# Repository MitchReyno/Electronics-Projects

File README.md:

# Electronics-Projects

A collection of various electronics projects I've worked on over the years.

## Categories

- [Eurorack](#eurorack) — Modular synthesizer modules
- [Nixie](#nixie) — Nixie tube and Dekatron display projects
- [Spice Models](#spice-models) — SPICE simulation models

---

## Eurorack

Eurorack-format modular synthesizer modules, designed in KiCad.

| Project                                              | Description                                                                                                                                      |
| ---------------------------------------------------- | ------------------------------------------------------------------------------------------------------------------------------------------------ |
| [Clocky](Eurorack/Clocky/)                           | Clock divider/multiplier — 8 gate outputs (÷/× per channel), RGB LED feedback, Arduino Nano firmware. Adapted from the SoundForce Clocky design. |
| [Dual Log/Linear VCA](Eurorack/Dual_Log_Linear_VCA/) | Dual voltage-controlled amplifier with switchable logarithmic and linear response curves.                                                        |
| [Eurorack PSU](Eurorack/Eurorack_PSU/)               | Eurorack power supply unit providing ±12 V and +5 V rails for a modular case.                                                                    |
| [LFO RW](Eurorack/LFO_RW/)                           | Low-frequency oscillator module with multiple waveform outputs.                                                                                  |
| [LFO VC](Eurorack/LFO_VC/)                           | Voltage-controlled LFO with CV over rate.                                                                                                        |
| [Quad Attenuator](Eurorack/Quad_Attenuator/)         | Four-channel passive/active attenuator panel.                                                                                                    |
| [VCA](Eurorack/VCA/)                                 | Voltage-controlled amplifier module.                                                                                                             |
| [VCF State Variable](Eurorack/VCF_State_Variable/)   | State-variable voltage-controlled filter with simultaneous low-pass, band-pass, and high-pass outputs.                                           |

---

## Nixie

High-voltage power supplies and display projects for Nixie and Dekatron tubes.

| Project                                     | Description                                                        |
| ------------------------------------------- | ------------------------------------------------------------------ |
| [Dekatron PSU MK1](Nixie/Dekatron_PSU_MK1/) | High-voltage power supply designed for Dekatron counting tubes.    |
| [Nixie PSU MK1](Nixie/Nixie_PSU_MK1/)       | High-voltage boost converter power supply for Nixie tube displays. |

---

## Spice Models

[`Spice_Models/`](Spice_Models/) — A library of SPICE simulation model files (`.MOD` / `.LIB`) for common components used across projects, including transistors, diodes, op-amps, regulators, and transformers.

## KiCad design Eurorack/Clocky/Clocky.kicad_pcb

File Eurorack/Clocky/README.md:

# Clocky

A Eurorack clock divider/multiplier module, adapted from the
[SoundForce Clocky](https://soundforce.nl) design.

## Overview

This is an adapted version of the **SoundForce Clocky** Eurorack clock divider/multiplier module. The original design uses a PCF8574P I2C I/O expander for reading 8 toggle switches and PL9823 addressable RGB LEDs for status display. This adaptation replaces both with simpler, non-I2C alternatives.

## What the module does

Clocky takes a single master clock input (via the TRG jack) and produces 8 independent gate outputs (A–H). Each output can either **divide** or **multiply** the incoming clock by a configurable ratio (default: ×1, ×2, ×4, ×8, ×16, ×3, ×5, ×7). A toggle switch per channel selects divide vs multiply mode. A RST jack resets the internal counter to re-synchronize divided outputs.

10 LEDs provide visual feedback:
- **LED0 (TRG):** Flashes on each incoming clock pulse (currently set to magenta/purple)
- **LED1 (RST):** Flashes green on reset
- **LED2–9 (A–H):** Show when each output fires — blue = divide mode, green = multiply mode

When no clock is connected, the LEDs run an idle rainbow animation.

## Hardware changes from original

| Subsystem | Original | Adapted version |
|-----------|----------|-----------------|
| Switch input | PCF8574P (I2C 8-bit expander) | CD74HC165E (parallel-in serial-out shift register) |
| LED display | 10× PL9823 (WS2812-compatible addressable RGB) | 10× common-anode RGB LEDs, multiplexed via CD4017BE decade counter |
| LED anode switching | N/A (PL9823 has integrated driver) | 10× 2N3904 NPN in emitter-follower config, driven by CD4017 outputs |
| LED cathode sinking | N/A | 3× 2N3904 NPN (one per color bus: R, G, B) |
| Current limiting | N/A | 3× resistors total (one per color bus, not per LED — safe because multiplexing ensures only one LED active at a time) |
| Libraries removed | Adafruit_NeoPixel, PCF8574, Wire | N/A |
| Libraries kept | elapsedMillis | elapsedMillis |

## Pin assignments

```
 Pin  | Function         | Group
------+------------------+------------------
 D0   | (reserved)       | Serial RX
 D1   | (reserved)       | Serial TX
 D2   | TRIG_PIN         | Inputs (INT0)
 D3   | RESET_PIN        | Inputs
 D4   | LED_R            | LED cathode sinks (PORTD bit 4)
 D5   | LED_G            | LED cathode sinks (PORTD bit 5)
 D6   | LED_B            | LED cathode sinks (PORTD bit 6)
 D7   | MUX_CLK          | LED mux (CD4017)
 D8   | MUX_RST          | LED mux (CD4017)
 D9   | SR_SH_LD         | Shift register (HC165)
 D10  | SR_CLK           | Shift register (HC165)
 D11  | SR_QH            | Shift register (HC165)
 D12  | OUT7 (G)         | Gate outputs (PORTB bit 4)
 D13  | OUT8 (H)         | Gate outputs (PORTB bit 5)
 A0   | OUT1 (A)         | Gate outputs (PORTC bit 0)
 A1   | OUT2 (B)         | Gate outputs (PORTC bit 1)
 A2   | OUT3 (C)         | Gate outputs (PORTC bit 2)
 A3   | OUT4 (D)         | Gate outputs (PORTC bit 3)
 A4   | OUT5 (E)         | Gate outputs (PORTC bit 4)
 A5   | OUT6 (F)         | Gate outputs (PORTC bit 5)
 A6   | (analog only)    | Unusable as digital
 A7   | (analog only)    | Unusable as digital
```

All 18 usable digital pins are assigned — zero spare. A6/A7 are analog-only on ATmega328P.

Port groupings:
- **PORTD bits 4–6** (D4/D5/D6): all three LED cathodes on the same port — allows single-register blanking in the ISR if needed
- **PORTC bits 0–5** (A0–A5): gate outputs A–F contiguous on one port
- **PORTB bits 4–5** (D12/D13): gate outputs G/H

## Pin constraints

- **D2 must be TRIG_PIN** — uses INT0 hardware interrupt (`attachInterrupt(INT0, trigger_int, CHANGE)`)
- **D0/D1** reserved for serial debugging
- **A6/A7** are analog-only on ATmega328P — cannot be digital outputs
- **D13** has onboard LED — will flicker with OUT8 (H) gate activity (acceptable)
- If an OLED display is wanted later, SDA/SCL (normally A4/A5) are occupied by gate outputs E and F — would require freeing pins, possibly by using an HC595 shift register for gate outputs to free up the PORTC pins

## Firmware files

All files live in the same Arduino sketch folder:

- **Clocky.ino** — Main sketch: setup, main loop (idle rainbow, reset handling, output timing, switch polling)
- **variables.h** — Pin definitions, LedColor struct, state variables, color constants, rainbow pattern
- **FastWrite.ino** — Port manipulation for fast gate output toggling (inverted logic: HIGH clears bit, LOW sets bit, because outputs drive 2N3904 open-collector stages)
- **LedMux.ino** — Timer2 ISR for LED multiplexing, CD4017 control, setLed() helper, rainbow/allOff functions
- **ShiftRegister.ino** — CD74HC165E reading (readSwitches byte, updateToggles with index remapping)
- **interrupts.ino** — Trigger ISR (clock rising/falling edge detection, divider/multiplier output firing, LED state updates)

## LED multiplexing design

### How it works
- **Timer2** configured in CTC mode at **10kHz** (prescaler 64, OCR2A = 24)
  - IMPORTANT: Prescaler 64 on ATmega328P Timer2 requires `(1 << CS22) | (1 << CS20)`, not `(1 << CS22)` alone (which is prescaler 256 = 2.5kHz = visible flicker)
- ISR fires every 100µs, cycling through 10 LEDs → each LED refreshes at 1kHz (flicker-free)
- ISR sequence: blank all cathodes → advance CD4017 clock → set cathodes for new LED
- The blanking-before-advance prevents ghosting (wrong color briefly showing on the next LED)

### NPN emitter-follower topology
- CD4017 Qn output (active HIGH) → 1k base resistor → 2N3904 NPN base
- NPN collector → +5V
- NPN emitter → LED common anode
- When Qn goes HIGH, emitter presents ~4.3V (5V - 0.7V Vbe) to LED anode
- With 3V LED Vf, ~1.3V across series resistor

### Floating anode problem
- When the NPN turns off, the LED anode floats (no discharge path)
- Parasitic capacitance holds the ~4.3V charge, taking 2-3 clock cycles to decay
- **Fix: 4.7k bleed resistor from each LED anode to GND** (10 resistors total)
- Provides fast discharge within the 100µs timeslot
- If still slow, try 2.2k or 1k

### Series resistors
- Only 3 resistors needed (one per color bus), NOT 30 (one per LED per color)
- Safe because multiplexing guarantees only one LED is powered at any given time
- Placed between shared cathode bus and NPN collector
- Values: ~68R for red (2V Vf), ~47-56R for green/blue (3.2V Vf) at 20mA
- Can push lower for higher instantaneous current to compensate for 10% duty cycle

## Switch reading (CD74HC165E)

- Polled every 50ms in main loop (no interrupt-driven detection)
- SH/LD pulsed low to latch parallel inputs, then 8 bits clocked out MSB-first on QH
- 10k pull-up resistors on each switch input (switch closed = GND = logic 0)
- `toggle_index[8] = {7,6,5,4,3,2,1,0}` reverses physical-to-logical mapping (from original design)

## Gate output stage

- Unchanged from original: Nano pin → 10k base resistor → 2N3904 NPN → output jack
- 10k collector pull-up to +5V
- Open-collector, active low: Nano HIGH = transistor ON = output LOW (gate pulse)
- FastWrite uses inverted port manipulation (LOW sets bit, HIGH clears bit)
- Port mapping: cases 0–5 use PORTC bits 0–5 (A0–A5), cases 6–7 use PORTB bits 4–5 (D12–D13)

## Trigger/Reset input conditioning

- 3.5mm jack → 100k resistor to GND → 2N3904 NPN base
- NPN collector pulled up to +5V via 10k
- Collector output to Arduino pin (inverted: external HIGH → NPN on → Arduino sees LOW)
- Handles Eurorack voltage levels (0-10V) safely — transistor clamps, Arduino only sees 0-5V
- **Both D2 and D3 need 10k pull-up resistors** to prevent floating/spurious triggering when no cable is connected

## Power supply

- Eurorack 10-pin header → +12V through 1N5819 Schottky (reverse protection) → 47µF decoupling → LM7805 → +5V
- 100nF ceramic on 7805 output
- Arduino powered via 5V pin (bypasses onboard regulator)
- Safe to have USB and circuit power connected simultaneously (Nano has built-in Schottky on USB 5V line)

## Known issues / bugs found and fixed

1. **Original FastWrite.ino bug:** Case 2 (D7) used `PORTD |= B11000000` which sets both bit 7 AND bit 6, accidentally also triggering output index 1. Fixed to only set bit 7.
2. **volatile struct copy:** `led_state[]` is `volatile LedColor` — C++ won't implicitly copy volatile structs. Must use member-by-member copy: `LedColor first = {led_state[0].r, led_state[0].g, led_state[0].b};`
3. **Timer2 prescaler:** CS22 alone = prescaler 256 (not 64). Need `(1 << CS22) | (1 << CS20)` for prescaler 64.
4. **PNP inversion problem:** CD4017 outputs are active-high, PNP turns on with base LOW → 9 LEDs on, 1 off (inverted). Solved by switching to NPN emitter-followers instead of PNPs.
5. **CD4017 CLK input:** Pure CMOS voltage-driven (no current needed), no Schmitt trigger hysteresis. Threshold ~2.5V at 5V supply. Direct drive from Arduino is clean enough; CD40106 buffer available if ringing occurs.

## Component inventory (relevant parts available)

- 100× 2N3904 (NPN), 100× 2N3906 (PNP), 20× BC327 (PNP), 20× BC337 (NPN)
- 25× CD74HC165E, 25× CD74HC595E, 2× SN74HC595N, 2× CD4094BE
- 29× CD4017BE
- 30× CD40106BE (Schmitt inverters — available if inversion needed)
- LM7805 regulators, 1N5819 Schottky diodes
- Common-anode RGB LEDs
- Full IC and semiconductor inventory available in CSV files

## Future considerations discussed but not implemented

- **BPM display:** 3-digit 7-segment or OLED (SSD1306). BPM = 60000000/period. Pin budget is the blocker — no spare pins.
- **Ratio display + live adjustment:** Single rotary encoder + OLED showing all 8 ratios. Would need pin reassignment (e.g., HC595 for gate outputs to free up pins for I2C).
- **ULN2803 Darlington array:** Could replace individual NPN transistors on cathode sinks if acquired, but not currently in inventory.

## KiCad schematic

A KiCad 8 schematic (.kicad_sch) and project file (.kicad_pro) were generated. The `lib_symbols` section is empty — KiCad resolves from local libraries on open. Layout needs manual cleanup after opening. Global labels connect the 6 sections (power, Arduino, switch input, LED driver, output buffers, trigger/reset inputs). Note: the KiCad schematic has NOT been updated to reflect the NPN emitter-follower change or the pin reassignment — it still shows the earlier PNP topology.

## Current build status

- Breadboarding stage
- LED multiplexing working after prescaler fix (10kHz confirmed on scope)
- NPN emitter-followers replacing original PNP attempt
- Bleed resistors (4.7k) needed on each LED anode to fix floating discharge
- Trigger/reset input conditioning circuit may not yet be wired — D2/D3 were floating and causing spurious triggers
- 10k pull-ups needed on D2 and D3

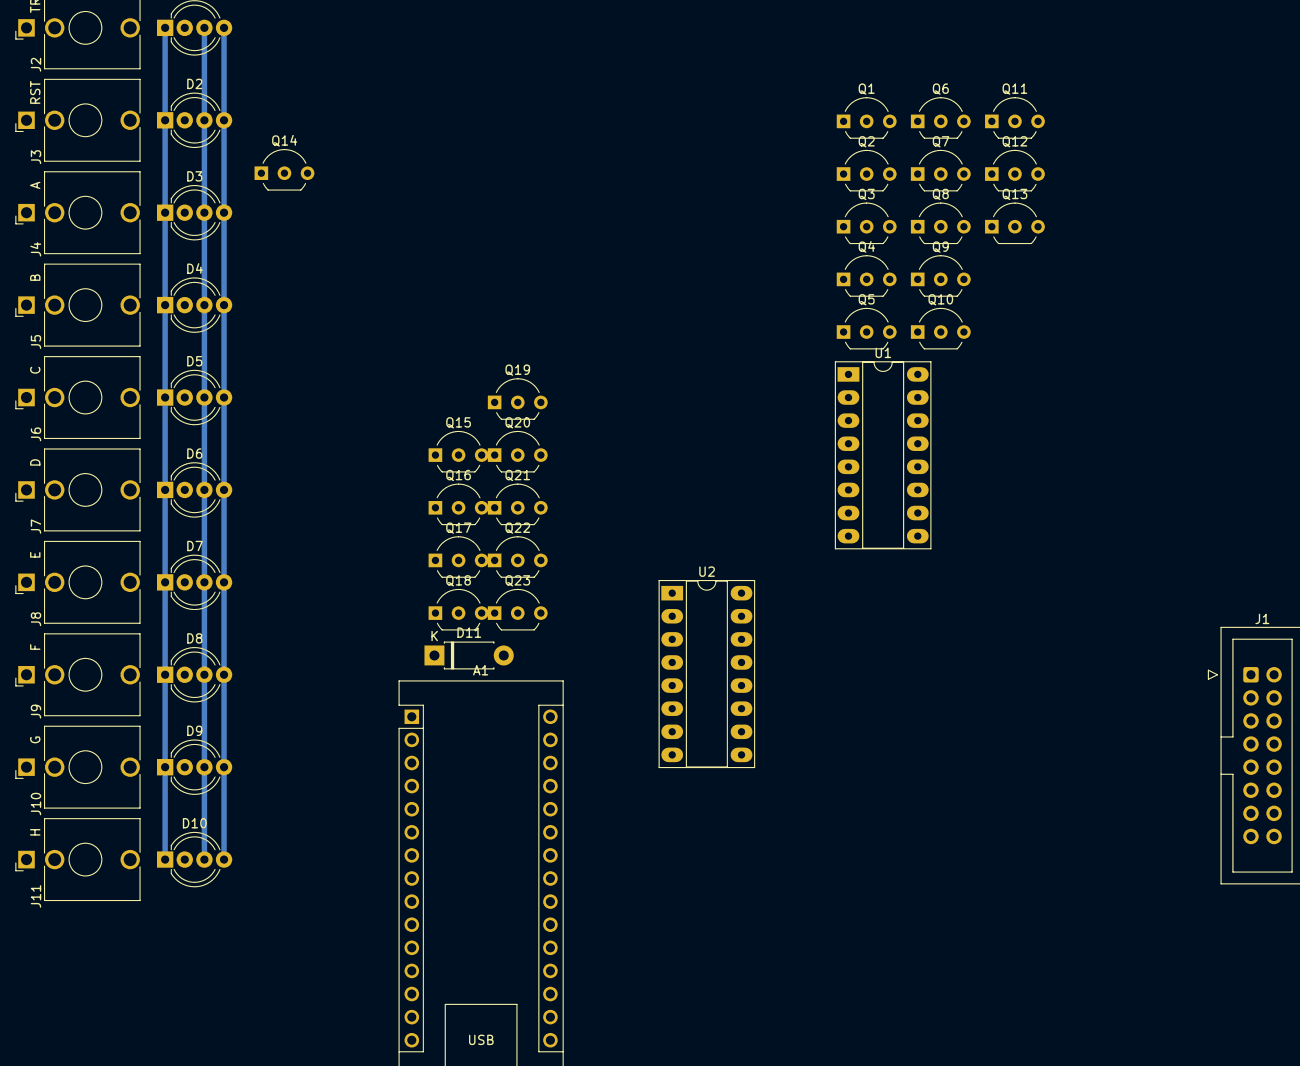
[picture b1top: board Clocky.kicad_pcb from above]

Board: 2 copper layers, 48 parts (0 on the bottom side), 31 nets.

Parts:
A1: Arduino_Nano_v3.x; Arduino_Nano
D1, D2, D3, D4, D5, D6, D7, D8, D9, D10: LED_RAGB; LED_D5.0mm-4_RGB_Wide_Pins
D11: 1N4740A; D_DO-41_SOD81_P7.62mm_Horizontal
J1: IDC_02x08; IDC-Header_2x08_P2.54mm_Vertical
J2: TRG; Jack_3.5mm_QingPu_WQP-PJ398SM_Vertical_CircularHoles
J3: RST; Jack_3.5mm_QingPu_WQP-PJ398SM_Vertical_CircularHoles
J4: A; Jack_3.5mm_QingPu_WQP-PJ398SM_Vertical_CircularHoles
J5: B; Jack_3.5mm_QingPu_WQP-PJ398SM_Vertical_CircularHoles
J6: C; Jack_3.5mm_QingPu_WQP-PJ398SM_Vertical_CircularHoles
J7: D; Jack_3.5mm_QingPu_WQP-PJ398SM_Vertical_CircularHoles
J8: E; Jack_3.5mm_QingPu_WQP-PJ398SM_Vertical_CircularHoles
J9: F; Jack_3.5mm_QingPu_WQP-PJ398SM_Vertical_CircularHoles
J10: G; Jack_3.5mm_QingPu_WQP-PJ398SM_Vertical_CircularHoles
J11: H; Jack_3.5mm_QingPu_WQP-PJ398SM_Vertical_CircularHoles
Q1, Q2, Q3, Q4, Q5, Q6, Q7, Q8, Q9, Q10, Q11, Q12, Q13, Q14, Q15, Q16, Q17, Q18, Q19, Q20, Q21, Q22, Q23: 2N3904; TO-92_Inline_Wide
U1: 4017; DIP-16_W7.62mm_Socket_LongPads
U2: 74HC165; DIP-16_W7.62mm_Socket_LongPads

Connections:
+5V: A1.27 (+5V), J1.11, J1.12, Q1.3 (C), Q2.3 (C), Q3.3 (C), Q4.3 (C), Q5.3 (C), Q6.3 (C), Q7.3 (C), Q8.3 (C), Q9.3 (C), Q10.3 (C), U1.16 (VDD), U2.16 (VCC)
+12V: J1.9, J1.10
/LED_Mux/LED_MUX_CLK: A1.10 (D7), U1.14 (CLK)
/LED_Mux/LED_MUX_RST: A1.11 (D8), U1.15 (Reset)
/Switches_SR/SR_CLK: A1.13 (D10), U2.2 (CP)
/Switches_SR/SR_PL_IN: A1.12 (D9), U2.1 (~PL)
/Switches_SR/SR_SER_OUT: A1.14 (D11), U2.9 (Q7)
GND: A1.4 (GND), A1.29 (GND), J1.3, J1.4, J1.5, J1.6, J1.7, J1.8, J2.S, J3.S, J4.S, J5.S, J6.S, J7.S, J8.S, J9.S, J10.S, J11.S, Q11.1 (E), Q12.1 (E), Q13.1 (E), Q14.1 (E), Q15.1 (E), Q16.1 (E), Q17.1 (E), Q18.1 (E), Q19.1 (E), Q20.1 (E), Q21.1 (E), Q22.1 (E), Q23.1 (E), U1.8 (VSS), U2.7 (~Q7), U2.8 (GND), U2.15 (~CE)
LED_B_BUS: D1.4 (BK), D2.4 (BK), D3.4 (BK), D4.4 (BK), D5.4 (BK), D6.4 (BK), D7.4 (BK), D8.4 (BK), D9.4 (BK), D10.4 (BK)
LED_G_BUS: D1.3 (GK), D2.3 (GK), D3.3 (GK), D4.3 (GK), D5.3 (GK), D6.3 (GK), D7.3 (GK), D8.3 (GK), D9.3 (GK), D10.3 (GK)
LED_R_BUS: D1.1 (RK), D2.1 (RK), D3.1 (RK), D4.1 (RK), D5.1 (RK), D6.1 (RK), D7.1 (RK), D8.1 (RK), D9.1 (RK), D10.1 (RK)
unnamed: A1.5 (D2), Q14.3 (C)
unnamed: A1.6 (D3), Q15.3 (C)
unnamed: D1.2 (A), Q1.1 (E)
unnamed: D2.2 (A), Q2.1 (E)
unnamed: D3.2 (A), Q3.1 (E)
unnamed: D4.2 (A), Q4.1 (E)
unnamed: D5.2 (A), Q5.1 (E)
unnamed: D6.2 (A), Q6.1 (E)
unnamed: D7.2 (A), Q7.1 (E)
unnamed: D8.2 (A), Q8.1 (E)
unnamed: D9.2 (A), Q9.1 (E)
unnamed: D10.2 (A), Q10.1 (E)
unnamed: J4.T, Q16.3 (C)
unnamed: J5.T, Q17.3 (C)
unnamed: J6.T, Q18.3 (C)
unnamed: J7.T, Q19.3 (C)
unnamed: J8.T, Q20.3 (C)
unnamed: J9.T, Q21.3 (C)
unnamed: J10.T, Q22.3 (C)
unnamed: J11.T, Q23.3 (C)

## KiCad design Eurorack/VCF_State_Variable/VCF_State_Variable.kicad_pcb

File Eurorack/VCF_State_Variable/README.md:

# VCF State Variable

A state-variable voltage-controlled filter (VCF) Eurorack module.

## What it does

The state-variable topology produces three simultaneous filter outputs from the same input signal:

| Output | Response  |
| ------ | --------- |
| LP     | Low-pass  |
| BP     | Band-pass |
| HP     | High-pass |

The module accepts up to three audio inputs and three CV inputs for cutoff frequency control. Resonance is also voltage-controllable via dedicated CV inputs on the cutoff board.

## Key components

| Component       | Role                                            |
| --------------- | ----------------------------------------------- |
| LM13700         | Dual OTA — voltage-controlled integrator stages |
| TL072           | Op-amp summation and buffering                  |
| 2N3904 / 2N3906 | NPN/PNP transistor linearisation stages         |
| 1N4148          | Clipping diodes                                 |

## Files

The design is split across two KiCad schematics:

| File                           | Contents                                          |
| ------------------------------ | ------------------------------------------------- |
| `VCF_State_Variable.kicad_sch` | Main filter board (signal path, I/O jacks, power) |
| `Cutoff_Board.kicad_sch`       | Cutoff and resonance CV processing sub-board      |

PCB and project files are in the root directory.

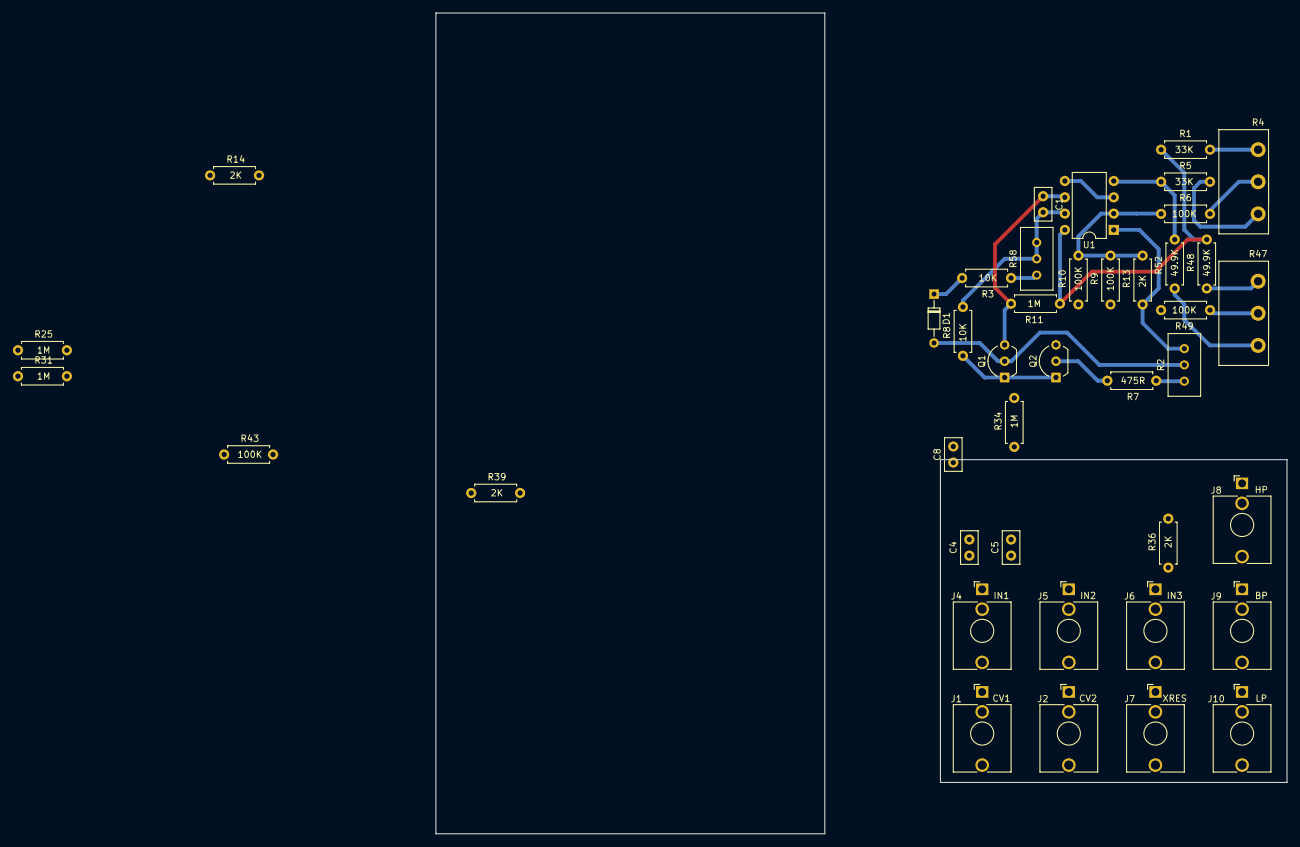
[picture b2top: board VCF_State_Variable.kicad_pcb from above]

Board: 2 copper layers, 132.6 x 127.9 mm, 41 parts (0 on the bottom side), 31 nets.

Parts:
C1: 100pF; C_Disc_D5.0mm_W2.5mm_P2.50mm
C4, C5, C8: 100nF; C_Disc_D5.0mm_W2.5mm_P2.50mm
D1: 1N4148; D_DO-34_SOD68_P7.62mm_Horizontal
J1: CV1; Jack_3.5mm_QingPu_WQP-PJ398SM_Vertical_CircularHoles
J2: CV2; Jack_3.5mm_QingPu_WQP-PJ398SM_Vertical_CircularHoles
J4: IN1; Jack_3.5mm_QingPu_WQP-PJ398SM_Vertical_CircularHoles
J5: IN2; Jack_3.5mm_QingPu_WQP-PJ398SM_Vertical_CircularHoles
J6: IN3; Jack_3.5mm_QingPu_WQP-PJ398SM_Vertical_CircularHoles
J7: XRES; Jack_3.5mm_QingPu_WQP-PJ398SM_Vertical_CircularHoles
J8: HP; Jack_3.5mm_QingPu_WQP-PJ398SM_Vertical_CircularHoles
J9: BP; Jack_3.5mm_QingPu_WQP-PJ398SM_Vertical_CircularHoles
J10: LP; Jack_3.5mm_QingPu_WQP-PJ398SM_Vertical_CircularHoles
Q1, Q2: 2N3904; TO-92_Inline_Wide
R1, R5: 33K; R_Axial_DIN0207_L6.3mm_D2.5mm_P7.62mm_Horizontal
R2: 100R; Potentiometer_Bourns_3296W_Vertical
R3, R8: 10K; R_Axial_DIN0207_L6.3mm_D2.5mm_P7.62mm_Horizontal
R4, R47: 100K; Potentiometer_Single_Horizontal
R6, R9, R10, R43, R49: 100K; R_Axial_DIN0207_L6.3mm_D2.5mm_P7.62mm_Horizontal
R7: 475R; R_Axial_DIN0207_L6.3mm_D2.5mm_P7.62mm_Horizontal
R11, R25, R31, R34: 1M; R_Axial_DIN0207_L6.3mm_D2.5mm_P7.62mm_Horizontal
R13, R14, R36, R39: 2K; R_Axial_DIN0207_L6.3mm_D2.5mm_P7.62mm_Horizontal
R48, R52: 49.9K; R_Axial_DIN0207_L6.3mm_D2.5mm_P7.62mm_Horizontal
R58: 100K; Potentiometer_Bourns_3296W_Vertical
U1: TL072; DIP-8_W7.62mm

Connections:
+12V: R1.2, R11.1, R48.2, U1.8 (V+)
-12V: R5.2, R52.2, U1.4 (V-)
/Cutoff_Board/ISUM_OUT: R25.2, R31.2, R34.2
CO1: R4.1, R5.1
CO2: R4.2, R6.1
CO3: R1.1, R4.3
GND: J1.S, J2.S, J4.S, J5.S, J6.S, J7.S, J8.S, J9.S, J10.S, Q2.2 (B), R7.1, U1.3 (+), U1.5 (+)
unnamed: C1.2, R8.1, R58.1, R58.2, U1.7
unnamed: C4.1, J4.T
unnamed: C4.2, R25.1
unnamed: C5.1, J5.T
unnamed: C5.2, R31.1
unnamed: C8.1, J6.T
unnamed: C8.2, R34.1
unnamed: D1.2 (A), Q1.2 (B), R2.2
unnamed: D1.1 (K), R3.1
unnamed: J1.T, R9.1
unnamed: J2.T, R10.1
unnamed: J7.T, R43.1
unnamed: J8.T, R14.1
unnamed: J9.T, R39.1
unnamed: J10.T, R36.1
unnamed: C1.1, Q1.3 (C), R11.2, U1.6 (-)
unnamed: Q1.1 (E), Q2.1 (E), R8.2
unnamed: R2.3, R7.2
unnamed: R3.2, R58.3
unnamed: R2.1, R13.2, U1.1
unnamed: R6.2, R9.2, R10.2, R13.1, U1.2 (-)
RES1: R47.1, R52.1
RES2: R47.2, R49.1
RES3: R47.3, R48.1

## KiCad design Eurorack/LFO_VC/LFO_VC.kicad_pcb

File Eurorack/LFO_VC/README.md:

# LFO VC

A voltage-controlled low-frequency oscillator (LFO) Eurorack module.

## What it does

Generates six simultaneous LFO waveforms with voltage control over rate:

| Output  | Waveform        |
| ------- | --------------- |
| SIN     | Sine            |
| TRI     | Triangle        |
| SAW     | Sawtooth        |
| RMP     | Ramp            |
| SQR     | Square          |
| INV_SQR | Inverted square |

CV input controls oscillator rate. A CV output is also provided.

## Key components

| Component         | Role                                           |
| ----------------- | ---------------------------------------------- |
| LM13700           | Dual OTA — oscillator core and CV gain control |
| TL072 (×5)        | Op-amp waveshapers and output buffers          |
| MPF102 JFET       | Triangle-to-sine waveshaping                   |
| 2N3904 / 2N3906   | NPN/PNP transistor stages                      |
| 10-pin IDC header | Eurorack ±12 V power                           |

## Files

KiCad 8 project files are in the root directory (`.kicad_sch`, `.kicad_pcb`, `.kicad_pro`).
A single-channel variant is available as `LFO_VC_Single.kicad_pcb`.
Fabrication outputs are in `Fab Outputs/`.

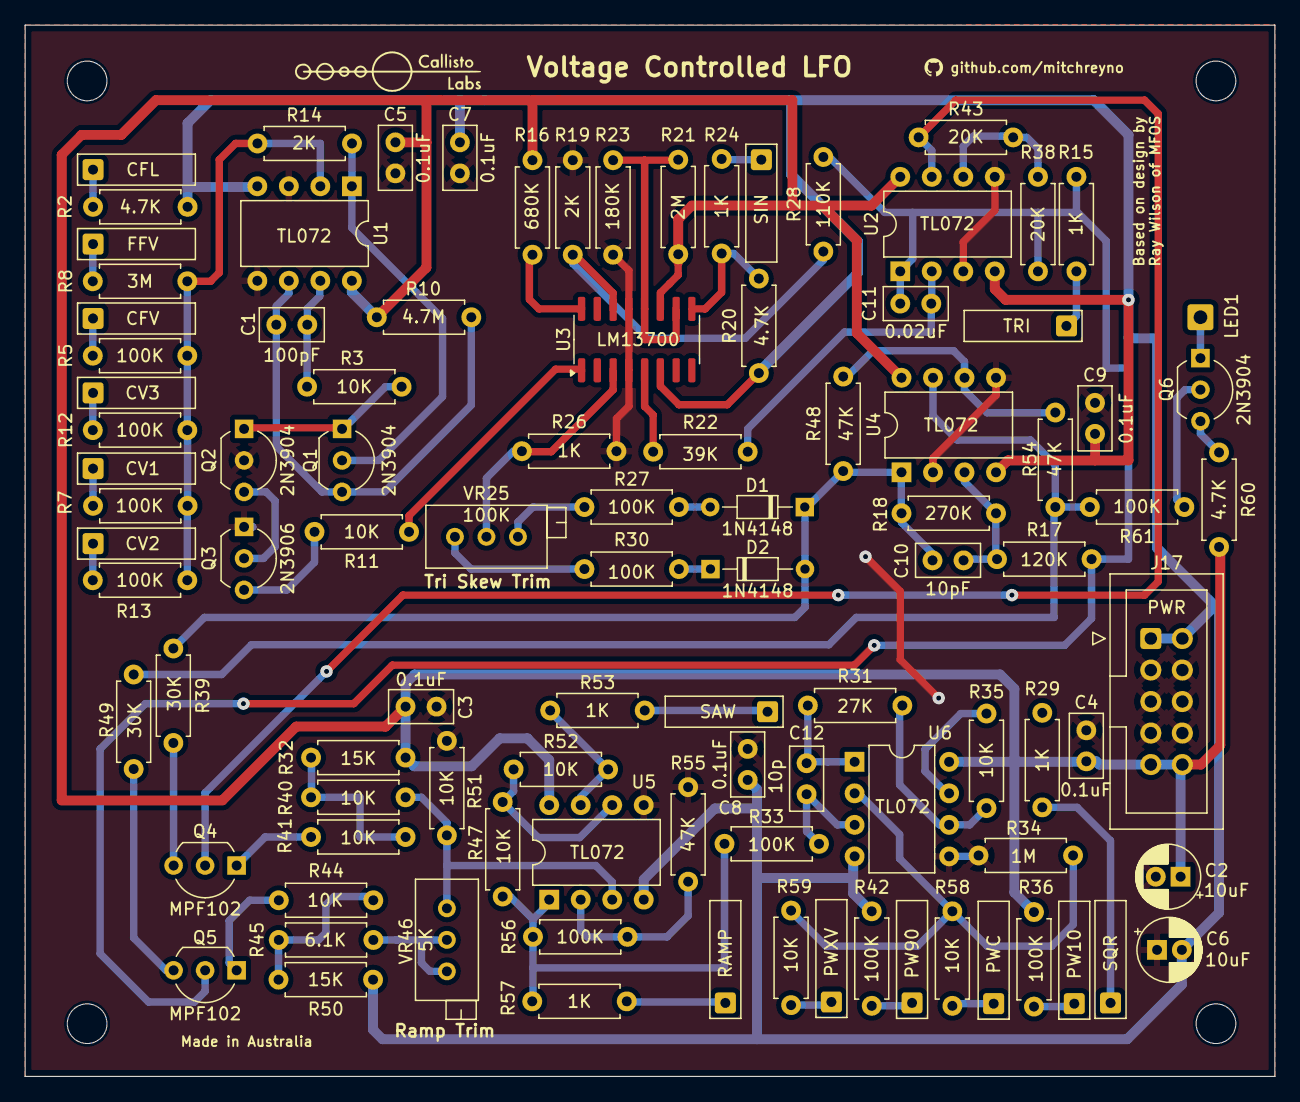
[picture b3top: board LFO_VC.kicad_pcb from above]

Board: 2 copper layers, 100.8 x 84.8 mm, 99 parts (0 on the bottom side), 64 nets.

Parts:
C1: 100pF; C_Disc_D5.0mm_W2.5mm_P2.50mm
C2, C6: 10uF; CP_Radial_D5.0mm_P2.00mm
C3, C4, C5, C7, C8, C9: 0.1uF; C_Disc_D5.0mm_W2.5mm_P2.50mm
C10: 10pF; C_Disc_D5.0mm_W2.5mm_P2.50mm
C11: 0.02uF; C_Disc_D5.0mm_W2.5mm_P2.50mm
C12: 10p; C_Disc_D5.0mm_W2.5mm_P2.50mm
D1, D2: 1N4148; D_DO-34_SOD68_P7.62mm_Horizontal
J1: CV1; SolderWire-0.127sqmm_1x01_D0.48mm_OD1mm_Custom
J2: CV2; SolderWire-0.127sqmm_1x01_D0.48mm_OD1mm_Custom
J3: CV3; SolderWire-0.127sqmm_1x01_D0.48mm_OD1mm_Custom
J4: TRI; SolderWire-0.127sqmm_1x01_D0.48mm_OD1mm_Custom
J5: SIN; SolderWire-0.127sqmm_1x01_D0.48mm_OD1mm_Custom
J6: SQR; SolderWire-0.127sqmm_1x01_D0.48mm_OD1mm_Custom
J7: SAW; SolderWire-0.127sqmm_1x01_D0.48mm_OD1mm_Custom
J8: RAMP; SolderWire-0.127sqmm_1x01_D0.48mm_OD1mm_Custom
J9: CFL; SolderWire-0.127sqmm_1x01_D0.48mm_OD1mm_Custom
J10: CFV; SolderWire-0.127sqmm_1x01_D0.48mm_OD1mm_Custom
J11: FFV; SolderWire-0.127sqmm_1x01_D0.48mm_OD1mm_Custom
J12: PWC; SolderWire-0.127sqmm_1x01_D0.48mm_OD1mm_Custom
J13: PW90; SolderWire-0.127sqmm_1x01_D0.48mm_OD1mm_Custom
J14: PW10; SolderWire-0.127sqmm_1x01_D0.48mm_OD1mm_Custom
J16: PWXV; SolderWire-0.127sqmm_1x01_D0.48mm_OD1mm_Custom
J17: PWR; IDC-Header_2x05_P2.54mm_Vertical
LED1: SolderWire-0.5sqmm_1x01_D0.9mm_OD2.1mm
Q1, Q2, Q6: 2N3904; TO-92_Inline_Wide
Q3: 2N3906; TO-92_Inline_Wide
Q4, Q5: MPF102; TO-92_Inline_Wide
R2, R20, R60: 4.7K; R_Axial_DIN0207_L6.3mm_D2.5mm_P7.62mm_Horizontal
R3, R11, R35, R40, R41, R44, R47, R51, R52, R58, R59: 10K; R_Axial_DIN0207_L6.3mm_D2.5mm_P7.62mm_Horizontal
R5, R7, R12, R13, R27, R30, R33, R36, R42, R56, R61: 100K; R_Axial_DIN0207_L6.3mm_D2.5mm_P7.62mm_Horizontal
R8: 3M; R_Axial_DIN0207_L6.3mm_D2.5mm_P7.62mm_Horizontal
R10: 4.7M; R_Axial_DIN0207_L6.3mm_D2.5mm_P7.62mm_Horizontal
R14, R19: 2K; R_Axial_DIN0207_L6.3mm_D2.5mm_P7.62mm_Horizontal
R15, R21, R26, R29, R53, R57: 1K; R_Axial_DIN0207_L6.3mm_D2.5mm_P7.62mm_Horizontal
R16: 680K; R_Axial_DIN0207_L6.3mm_D2.5mm_P7.62mm_Horizontal
R17: 120K; R_Axial_DIN0207_L6.3mm_D2.5mm_P7.62mm_Horizontal
R18: 270K; R_Axial_DIN0207_L6.3mm_D2.5mm_P7.62mm_Horizontal
R22: 39K; R_Axial_DIN0207_L6.3mm_D2.5mm_P7.62mm_Horizontal
R23: 180K; R_Axial_DIN0207_L6.3mm_D2.5mm_P7.62mm_Horizontal
R24: 2M; R_Axial_DIN0207_L6.3mm_D2.5mm_P7.62mm_Horizontal
R28: 110K; R_Axial_DIN0207_L6.3mm_D2.5mm_P7.62mm_Horizontal
R31: 27K; R_Axial_DIN0207_L6.3mm_D2.5mm_P7.62mm_Horizontal
R32, R50: 15K; R_Axial_DIN0207_L6.3mm_D2.5mm_P7.62mm_Horizontal
R34: 1M; R_Axial_DIN0207_L6.3mm_D2.5mm_P7.62mm_Horizontal
R38, R43: 20K; R_Axial_DIN0207_L6.3mm_D2.5mm_P7.62mm_Horizontal
R39, R49: 30K; R_Axial_DIN0207_L6.3mm_D2.5mm_P7.62mm_Horizontal
R45: 6.1K; R_Axial_DIN0207_L6.3mm_D2.5mm_P7.62mm_Horizontal
R48, R54, R55: 47K; R_Axial_DIN0207_L6.3mm_D2.5mm_P7.62mm_Horizontal
U1, U2, U4, U5, U6: TL072; DIP-8_W7.62mm
U3: LM13700; SOIC-16_3.9x9.9mm_P1.27mm
VR25: 100K; Potentiometer_Bourns_3296X_Horizontal
VR46: 5K; Potentiometer_Bourns_3296X_Horizontal

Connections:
+12V: C2.1, C3.1, C4.1, C5.1, J17.9, J17.10, R10.1, R16.2, R24.2, R32.2, R36.2, R60.2, U1.8 (V+), U2.8 (V+), U3.11 (V+), U4.8 (V+), U5.8 (V+), U6.8 (V+)
-12V: C6.2, C7.2, C8.2, C9.2, J17.1, J17.2, R2.2, R20.1, R42.1, R50.1, U1.4 (V-), U2.4 (V-), U3.6 (V-), U4.4 (V-), U5.4 (V-), U6.4 (V-)
/INV_SQR: R49.1, R54.1, R61.2, U4.7
/RMP: J8.1 (T), R57.1
/SAW: J7.1 (T), R53.1
/SIN: J5.1 (T), R21.2
/SQR: J6.1 (T), R29.2
/TRI: J4.1 (T), R15.1
CV_OUTPUT: R11.1, U3.1 (BIAS_INPUT)
GND: C2.2, C3.2, C4.2, C5.2, C6.1, C7.1, C8.1, C9.1, J17.3, J17.4, J17.5, J17.6, J17.7, J17.8, Q2.2 (B), Q3.1 (E), R19.2, R23.1, R26.2, R34.1, R51.1, R55.2, U1.3 (+), U1.5 (+), U2.3 (+), U2.5 (+), U3.4 (-), U3.13 (-), U4.2 (-), U4.5 (+), U5.5 (+), U6.5 (+)
unnamed: C1.2, R3.2, U1.7
unnamed: C12.2, R31.1, U6.1
unnamed: D1.2 (A), R27.2
unnamed: C10.2, D1.1 (K), D2.2 (A), R18.1, R39.1, R48.1, U4.1
unnamed: D2.1 (K), R30.2
unnamed: J1.1 (T), R7.1
unnamed: J2.1 (T), R13.2
unnamed: J3.1 (T), R12.2
unnamed: J9.1, R2.1
unnamed: J10.1, R5.2
unnamed: J11.1, R8.2
unnamed: J12.1, R58.1
unnamed: J13.1, R42.2
unnamed: J14.1, R36.1
unnamed: J16.1 (T), R59.1
unnamed: LED1.1 (A), Q6.1 (E)
unnamed: Q1.2 (B), R14.1, U1.1
unnamed: C1.1, Q1.3 (C), R10.2, U1.6 (-)
unnamed: Q1.1 (E), Q2.1 (E), R3.1
unnamed: Q2.3 (C), Q3.2 (B)
unnamed: Q3.3 (C), R11.2
unnamed: Q4.1 (D), R41.1
unnamed: Q4.3 (G), R39.2
unnamed: Q4.2 (S), R43.2, U2.7
unnamed: Q5.1 (D), R44.1
unnamed: Q5.3 (G), R49.2
unnamed: C11.1, Q5.2 (S), R15.2, R17.2, R28.2, R38.1, U2.1
unnamed: Q6.2 (B), R61.1
unnamed: Q6.3 (C), R60.1
unnamed: R27.1, VR25.3
unnamed: R29.1, R35.1, U6.7
unnamed: R30.1, VR25.1
unnamed: R32.1, R40.1, R41.2
unnamed: R33.1, R47.1, R56.1, R57.2, U5.1
unnamed: R44.2, R45.1, R50.2
unnamed: R45.2, VR46.2, VR46.3
unnamed: R52.1, R53.2, U5.7
unnamed: R5.1, R7.2, R8.1, R12.1, R13.1, R14.2, U1.2 (-)
unnamed: C11.2, R22.2, U2.2 (-)
unnamed: R38.2, R43.1, U2.6 (-)
unnamed: R26.1, U3.3 (+), VR25.2
unnamed: R22.1, U3.5 (OUTPUT)
unnamed: R23.2, R24.1, U3.10 (BUFF_IN), U3.12 (OUTPUT)
unnamed: R20.2, R21.1, U3.9 (BUFF_OUT)
unnamed: R19.1, R28.1, U3.14 (+)
unnamed: R16.1, U3.16 (BIAS_INPUT)
unnamed: C10.1, R17.1, R18.2, U4.3 (+)
unnamed: R48.2, R54.2, U4.6 (-)
unnamed: R40.2, R51.2, U5.3 (+), VR46.1
unnamed: R55.1, R56.2, U5.2 (-)
unnamed: R47.2, R52.2, U5.6 (-)
unnamed: C12.1, R33.2, U6.3 (+)
unnamed: R34.2, R58.2, R59.2, U6.2 (-)
unnamed: R31.2, R35.2, U6.6 (-)

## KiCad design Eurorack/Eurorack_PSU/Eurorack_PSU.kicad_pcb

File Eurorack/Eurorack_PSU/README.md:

# Eurorack PSU

A mains-powered linear power supply for a Eurorack modular synthesizer case.

## What it does

Converts 240 VAC mains to the four standard Eurorack DC rails:

| Rail  | Regulator |
| ----- | --------- |
| +12 V | LM7812    |
| −12 V | LM7912    |
| +5 V  | LM7805    |
| −5 V  | LM7905    |

## Key components

| Component                         | Role                          |
| --------------------------------- | ----------------------------- |
| Mains transformer (240 VAC, 20:1) | Mains isolation and step-down |
| GBU6A                             | Full-bridge rectifier         |
| LM7812 / LM7912                   | ±12 V linear regulators       |
| LM7805 / LM7905                   | ±5 V linear regulators        |
| 10 000 µF bulk caps               | Reservoir filtering           |
| 1N4007 diodes                     | Rectifier protection          |

## Files

KiCad 8 project files are in the root directory (`.kicad_sch`, `.kicad_pcb`, `.kicad_pro`).

**Revision:** 1 (2026-02-28)

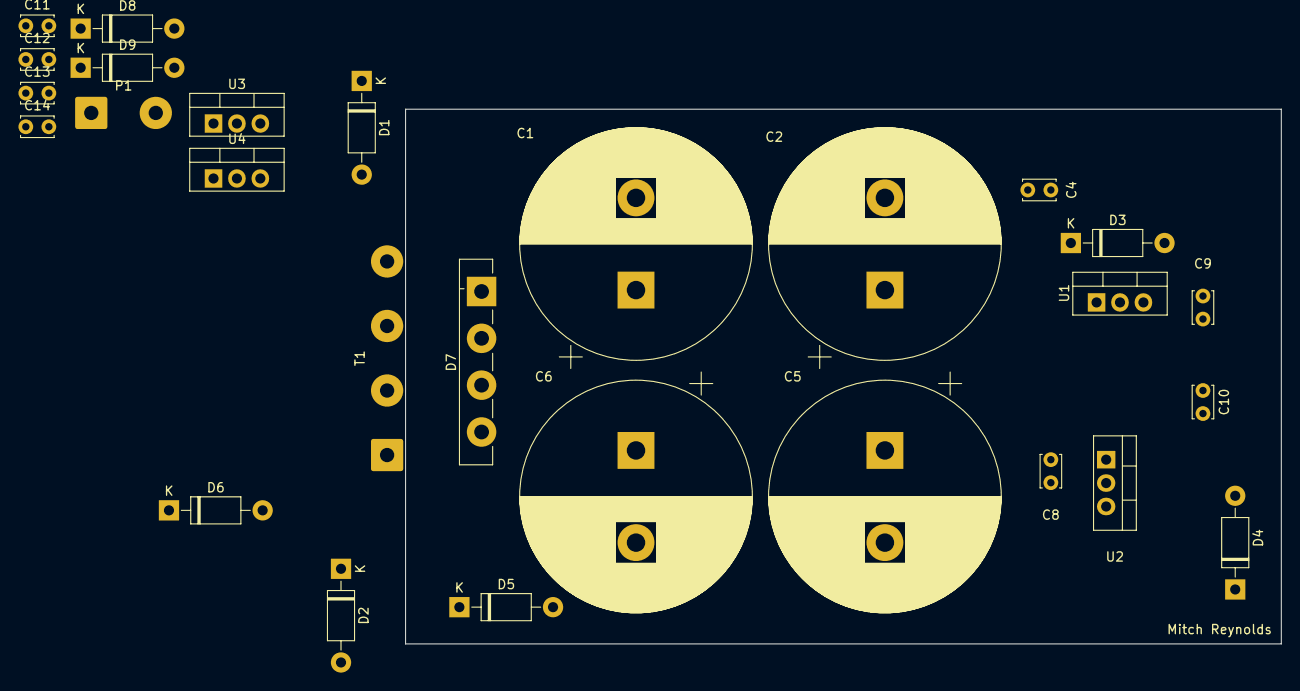
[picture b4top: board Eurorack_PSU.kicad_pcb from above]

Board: 2 copper layers, 95.0 x 58.0 mm, 27 parts (0 on the bottom side), 10 nets, no tracks yet.

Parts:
C1, C2, C5, C6: 10000uF; CP_Radial_D25.0mm_P10.00mm_SnapIn
C4, C8, C9, C10, C11, C12, C13, C14: 1uF; C_Disc_D3.4mm_W2.1mm_P2.50mm
D1, D2, D3, D4, D5, D6, D8, D9: 1N4007; D_DO-41_SOD81_P10.16mm_Horizontal
D7: GBU6A; Diode_Bridge_Vishay_GBU
P1: 240VAC 50Hz; SolderWire-0.75sqmm_1x02_P7mm_D1.25mm_OD3.5mm
T1: 20:1; SolderWire-0.75sqmm_1x04_P7mm_D1.25mm_OD3.5mm
U1: LM7812; TO-220-3_Vertical
U2: LM7912; TO-220-3_Vertical
U3: LM7805; TO-220-3_Vertical
U4: LM7905; TO-220-3_Vertical

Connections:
0: C1.2, C2.2, C4.2, C5.1, C6.1, C8.2, C9.2, C10.2, C11.2, C12.2, C13.2, C14.2, D2.2 (A), D5.2 (A), D6.1 (K), D9.1 (K), T1.4 (SB), U1.2 (GND), U2.1 (GND), U3.2 (GND), U4.1 (GND)
+5V: C12.1, D1.2 (A), D2.1 (K), U3.3 (VO)
+12V: C9.1, D3.2 (A), D5.1 (K), U1.3 (VO)
-5V: C14.1, D8.1 (K), D9.2 (A), U4.3 (VO)
-12V: C10.1, D4.1 (K), D6.2 (A), U2.3 (VO)
unnamed: C1.1, C2.1, C4.1, C11.1, D1.1 (K), D3.1 (K), D7.1 (+), U1.1 (VI), U3.1 (VI)
unnamed: C5.2, C6.2, C8.1, C13.1, D4.2 (A), D7.4 (-), D8.2 (A), U2.2 (VI), U4.2 (VI)
unnamed: P1.1 (L), T1.1 (AA)
unnamed: P1.2 (N), T1.2 (AB)
unnamed: D7.3, T1.3 (SA)

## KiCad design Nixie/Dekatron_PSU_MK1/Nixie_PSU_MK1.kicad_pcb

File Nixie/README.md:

# Nixie

High-voltage power supply projects for Nixie and Dekatron display tubes.

## Projects

| Project                               | Description                                                      |
| ------------------------------------- | ---------------------------------------------------------------- |
| [Nixie PSU MK1](Nixie_PSU_MK1/)       | Boost converter providing ~170 V DC for Nixie tube displays      |
| [Dekatron PSU MK1](Dekatron_PSU_MK1/) | High-voltage boost converter adapted for Dekatron counting tubes |

Both PSUs are built around the **MC34063AP** switching regulator IC with an **IRF740** N-channel MOSFET as the power switch.

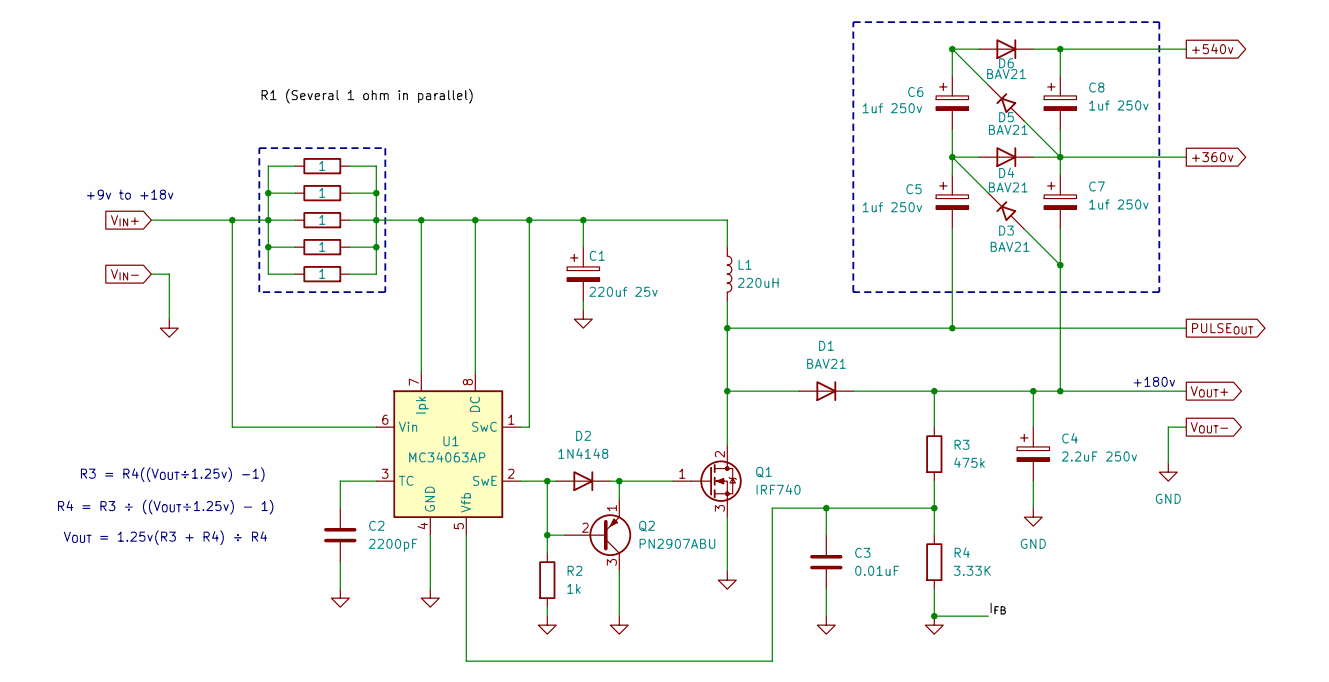
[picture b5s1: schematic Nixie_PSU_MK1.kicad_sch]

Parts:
C1: 220uf 25v; CP_Radial_D8.0mm_P3.50mm
C2: 2200pF; C_Disc_D3.4mm_W2.1mm_P2.50mm
C3: 0.01uF; C_Disc_D3.4mm_W2.1mm_P2.50mm
C4: 2.2uF 250v; CP_Radial_D10.0mm_P7.50mm
C5, C6, C7, C8: 1uf 250v; CP_Radial_D6.3mm_P2.50mm
D1, D3, D4, D5, D6: BAV21; D_DO-35_SOD27_P7.62mm_Horizontal
D2: 1N4148; D_DO-35_SOD27_P7.62mm_Horizontal
L1: 220uH; SolderWire-0.75sqmm_1x02_P4.8mm_D1.25mm_OD2.3mm
Q1: IRF740; TO-220-3_Vertical
Q2: PN2907ABU; TO-92_Wide
R1a1, R1b1, R1c1, R1d1, R1e1: 1; R_Axial_DIN0207_L6.3mm_D2.5mm_P7.62mm_Horizontal
R2: 1k; R_Axial_DIN0207_L6.3mm_D2.5mm_P7.62mm_Horizontal
R3: 475k; R_Axial_DIN0207_L6.3mm_D2.5mm_P7.62mm_Horizontal
R4: 3.33K; R_Axial_DIN0207_L6.3mm_D2.5mm_P7.62mm_Horizontal
U1: MC34063AP; DIP-8_W7.62mm

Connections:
+360v: C7.1, C8.2, D4.1 (K), D5.2 (A)
+540v: C8.1, D6.1 (K)
unnamed: D2.2 (A), Q2.2 (B), R2.1, U1.2 (SwE)
unnamed: D2.1 (K), Q1.1 (G), Q2.1 (E)
unnamed: C5.1, C6.2, D3.1 (K), D4.2 (A)
unnamed: C6.1, D5.1 (K), D6.2 (A)
unnamed: C1.1, L1.1, R1a1.2, R1b1.2, R1c1.2, R1d1.2, R1e1.2, U1.1 (SwC), U1.7 (Ipk), U1.8 (DC)
unnamed: C2.1, U1.3 (TC)
unnamed: C3.1, R3.2, R4.1, U1.5 (Vfb)
PULSE_{OUT}: C5.2, D1.2 (A), L1.2, Q1.2 (D)
V_{IN}+: R1a1.1, R1b1.1, R1c1.1, R1d1.1, R1e1.1, U1.6 (Vin)
V_{IN}-: C1.2, C2.2, C3.2, C4.2, Q1.3 (S), Q2.3 (C), R2.2, R4.2, U1.4 (GND)
V_{OUT}+: C4.1, C7.2, D1.1 (K), D3.2 (A), R3.1

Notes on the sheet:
V_{OUT} = 1.25v(R3 + R4) ÷ R4
R4 = R3 ÷ ((V_{OUT}÷1.25v) - 1)
+9v to +18v
+180v
R3 = R4((V_{OUT}÷1.25v) -1)

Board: 2 copper layers, 26 parts (0 on the bottom side), 13 nets, no tracks yet.

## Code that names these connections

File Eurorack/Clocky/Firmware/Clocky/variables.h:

// =============================================================
// Clocky Alt — variables.h
// Shift register (HC165) + multiplexed RGB LED (CD4017) version
// =============================================================

#ifndef VARIABLES_H
#define VARIABLES_H

// --- Pin definitions ---
//
// Pin grouping by port:
//   Port D (D0–D7): serial, inputs, LED cathodes, 4017 CLK
//   Port B (D8–D13): 4017 RST, shift register, gate outputs G/H
//   Port C (A0–A5): gate outputs A–F

// Trigger & Reset inputs (active-low via 2N3904 inverters)
#define TRIG_PIN        2   // D2 — external trigger input (INT0)
#define RESET_PIN       3   // D3 — external reset input

// Gate/trigger outputs (active-low open-collector)
// outs[0]=OUT_A .. outs[7]=OUT_H
// A0–A5 = outputs A–F (PORTC bits 0–5), D12/D13 = outputs G/H (PORTB bits 4–5)
const byte outs[8] = {A0, A1, A2, A3, A4, A5, 12, 13};

// CD4017BE decade counter (LED anode multiplexing via NPN emitter-followers)
// Each 4017 Qn output drives a 2N3904 base; collector to +5V,
// emitter to LED common anode. Active-high: Q HIGH = LED powered.
#define LED_MUX_CLK_PIN 7   // D7 — Clock input to CD4017
#define LED_MUX_RST_PIN 8   // D8 — Reset input to CD4017

// RGB cathode sink transistors (2N3904 NPN, active-high base drive)
// All three are on PORTD (bits 4–6) — grouped for fast simultaneous blanking.
// NOTE: A6 and A7 are ANALOG-ONLY on ATmega328P — cannot be used as digital outputs.
#define LED_R_PIN       4   // D4 — Red cathode sink   (PD4)
#define LED_G_PIN       5   // D5 — Green cathode sink (PD5)
#define LED_B_PIN       6   // D6 — Blue cathode sink  (PD6)

// CD74HC165E shift register (switch reading)
#define SR_SH_LD_PIN    9   // D9  — SH/LD: pulse low to latch parallel inputs
#define SR_CLK_PIN      10  // D10 — CLK: clock to shift data out
#define SR_QH_PIN       11  // D11 — QH: serial data out
// No interrupt pin for switch change — all interrupt-capable pins are in use; poll instead.

// --- LED color definitions ---
// Each LED has an RGB triplet stored as {R, G, B} where 1=on, 0=off
// For the multiplexed scheme, each "color" is just which cathodes to sink.
// Index 0 = TRG indicator, 1 = RST indicator, 2–9 = steps A–H
// These are the DEFAULT idle colors (the rainbow pattern equivalent).

// Simple on/off per channel (no PWM color mixing for now)
struct LedColor {
  uint8_t r;  // 0 or 1
  uint8_t g;  // 0 or 1
  uint8_t b;  // 0 or 1
};

// Current display state for all 10 LEDs
// Updated by main loop / ISR, read by the mux timer ISR
volatile LedColor led_state[10] = {
  {0, 0, 0},  // LED0: TRG indicator (off at startup)
  {0, 0, 0},  // LED1: RST indicator
  {0, 0, 0},  // LED2: Step A
  {0, 0, 0},  // LED3: Step B
  {0, 0, 0},  // LED4: Step C
  {0, 0, 0},  // LED5: Step D
  {0, 0, 0},  // LED6: Step E
  {0, 0, 0},  // LED7: Step F
  {0, 0, 0},  // LED8: Step G
  {0, 0, 0},  // LED9: Step H
};

// Predefined colors (on/off only — no PWM)
const LedColor COLOR_OFF     = {0, 0, 0};
const LedColor COLOR_RED     = {1, 0, 0};
const LedColor COLOR_GREEN   = {0, 1, 0};
const LedColor COLOR_BLUE    = {0, 0, 1};
const LedColor COLOR_YELLOW  = {1, 1, 0};
const LedColor COLOR_CYAN    = {0, 1, 1};
const LedColor COLOR_MAGENTA = {1, 0, 1};
const LedColor COLOR_WHITE   = {1, 1, 1};

// Color used for divider mode output active
const LedColor COLOR_DIVIDE  = COLOR_BLUE;
// Color used for multiplier mode output active
const LedColor COLOR_MULT    = COLOR_GREEN;
// Color for trigger flash
const LedColor COLOR_TRIG    = COLOR_MAGENTA;
// Color for reset flash
const LedColor COLOR_RESET   = COLOR_RED;

// --- Rainbow idle colors (one per LED, static assignment) ---
// Approximation of the original PL9823 rainbow using on/off RGB
const LedColor rainbow_colors[10] = {
  {1, 0, 0},  // LED0 (TRG): red
  {1, 0, 0},  // LED1 (RST): red
  {1, 1, 0},  // LED2 (A): yellow
  {1, 1, 0},  // LED3 (B): yellow
  {0, 1, 0},  // LED4 (C): green
  {0, 1, 1},  // LED5 (D): cyan
  {0, 0, 1},  // LED6 (E): blue
  {0, 0, 1},  // LED7 (F): blue
  {1, 0, 1},  // LED8 (G): magenta
  {1, 1, 1},  // LED9 (H): white
};

// --- Clock / sequencer state ---
bool out_state[8] = {0, 0, 0, 0, 0, 0, 0, 0};

int clock_counter = 0;
byte reset_counter = 0;
unsigned long clock_length = 10000;

bool do_we_know_the_period_yet = 0;

unsigned long time_turned_on[8]    = {0, 0, 0, 0, 0, 0, 0, 0};
unsigned long trigger_time;
unsigned long trigger_on_time;
unsigned long previous_trigger_on_time;
unsigned long trigger_off_time;
unsigned long reset_on_time;
unsigned long reset_off_time;
unsigned long last_trigger_on_time = 0;

volatile bool read_toggles = 0;

bool reset_actual   = 0;
bool reset_previous = 0;
volatile bool show_leds = 0;

bool toggle_divide[8] = {1, 1, 1, 1, 1, 1, 1, 1};
// Mapping: physical switch index → logical output index (reversed)
byte toggle_index[8]  = {7, 6, 5, 4, 3, 2, 1, 0};

unsigned long period = 0;

int before = 0;
int after  = 0;

bool waiting_for_clock    = 1;
unsigned long time_to_rainbow = 0;

// LED multiplexing state
volatile byte current_led = 0;  // 0–9, which LED the 4017 is currently driving

#endif

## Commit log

2026-02-27 Add initial spice models
2026-02-27 Add initial eurorack projects
2026-02-27 Add initial nixie projects
2026-02-28 Update PSU and add more spice models
2026-03-01 Add more spice models
2026-03-01 Rename LFO-VC to LFO_VC
2026-03-01 add LFO_RW
2026-04-04 Add Callisto Labs logo
2026-04-04 Update LFO_VC with fab outputs
2026-04-04 Update LFO_RW faceplate
2026-04-04 Add Quad Attenutator
2026-04-04 Update Nixie PSU
2026-04-04 Add initial files for Dual Log Linear VCA
2026-04-12 Add Clocky module
2026-04-12 Add docs
2026-04-12 Add VCA intial project
2026-04-12 Add VCF intial project
2026-04-12 Format MD files
2026-05-04 Update finalised clocky files
